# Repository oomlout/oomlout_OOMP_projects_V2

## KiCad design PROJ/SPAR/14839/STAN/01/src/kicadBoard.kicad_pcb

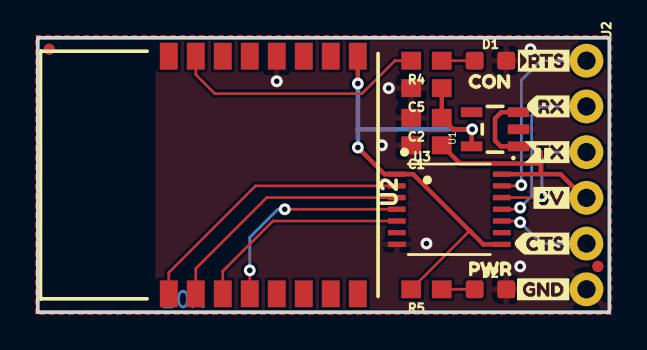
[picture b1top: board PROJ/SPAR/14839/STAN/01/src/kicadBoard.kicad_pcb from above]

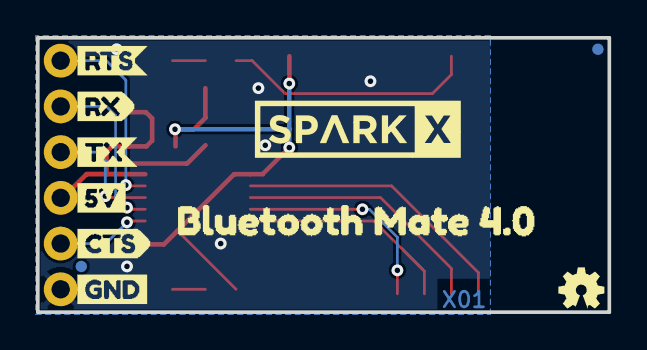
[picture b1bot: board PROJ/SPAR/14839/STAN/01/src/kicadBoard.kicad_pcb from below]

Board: 2 copper layers, 31.8 x 15.2 mm, 33 parts (11 on the bottom side), 14 nets.

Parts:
C1, C5: 1.0uF; 0603
C2: 0.1uF; 0603
D1: GREEN; LED-0603
D2: RED; LED-0603
FD1, FD2, FD3, FD4: FIDUCIALUFIDUCIAL; FIDUCIAL-MICRO
FRAME1: FRAME-LETTER; CREATIVE_COMMONS
J2: 1X06_NO_SILK
LOGO1: OSHW-LOGOMINI; OSHW-LOGO-MINI
LOGO3: SPARKX-LOGO5; SPARKX-LARGE
R4: 330; 0603
R5: 1k; 0603
U1: 3.3V; SOT23-5
U2: HM-17; HM-11
U3: TXB0104; TSSOP14
U$1: CTS13
U$2: 5V9
U$3: GND8
U$4: RX10
U$5: TX9
U$6: RTS12
U$7: RTS13
U$8: TX11
U$9: RX9
U$10: 5V6
U$11: CTS8
U$12: GND13
U$13: BLUETOOTH_MATE_4#06
U$14: PWR6
U$15: CON7

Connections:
3.3V: C2.1, C5.1, R5.2, U1.5, U2.9, U3.1, U3.8
5V: C1.1, J2.4, U1.1, U1.3, U3.14
5V_BT_CTS: J2.5, U3.10
5V_BT_RTS: J2.1, U3.13
5V_BT_RX: J2.2, U3.11
5V_BT_TX: J2.3, U3.12
BT_CTS: U2.3, U3.5
BT_RTS: U2.1, U3.2
BT_RX: U2.4, U3.4
BT_TX: U2.2, U3.3
GND: C1.2, C2.2, C5.2, D1.C, D2.C, J2.6, U1.2, U2.12, U3.7
unnamed: D1.A, R4.1
unnamed: D2.A, R5.1
PIO1/LED: R4.2, U2.15

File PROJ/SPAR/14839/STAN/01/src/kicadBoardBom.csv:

"Id";"Designator";"Package";"Quantity";"Designation";"Supplier and ref";
1;"U$15";"CON7";1;"";;;
2;"U$6";"RTS12";1;"";;;
3;"U2";"HM-11";1;"HM-17";;;
4;"FRAME1";"CREATIVE_COMMONS";1;"FRAME-LETTER";;;
5;"U$14";"PWR6";1;"";;;
6;"U$3";"GND8";1;"";;;
7;"U$1";"CTS13";1;"";;;
8;"R4";"0603";1;"330";;;
9;"D1";"LED-0603";1;"GREEN";;;
10;"U1";"SOT23-5";1;"3.3V";;;
11;"R5";"0603";1;"1k";;;
12;"C2";"0603";1;"0.1uF";;;
13;"J2";"1X06_NO_SILK";1;"";;;
14;"C1,C5";"0603";2;"1.0uF";;;
15;"U3";"TSSOP14";1;"TXB0104";;;
16;"FD1,FD2,FD4,FD3";"FIDUCIAL-MICRO";4;"FIDUCIALUFIDUCIAL";;;
17;"U$2";"5V9";1;"";;;
18;"U$4";"RX10";1;"";;;
19;"U$5";"TX9";1;"";;;
20;"D2";"LED-0603";1;"RED";;;
21;"U$12";"GND13";1;"";;;
22;"U$9";"RX9";1;"";;;
23;"U$7";"RTS13";1;"";;;
24;"LOGO1";"OSHW-LOGO-MINI";1;"OSHW-LOGOMINI";;;
25;"U$10";"5V6";1;"";;;
26;"LOGO3";"SPARKX-LARGE";1;"SPARKX-LOGO5";;;
27;"U$8";"TX11";1;"";;;
28;"U$13";"BLUETOOTH_MATE_4#06";1;"";;;
29;"U$11";"CTS8";1;"";;;

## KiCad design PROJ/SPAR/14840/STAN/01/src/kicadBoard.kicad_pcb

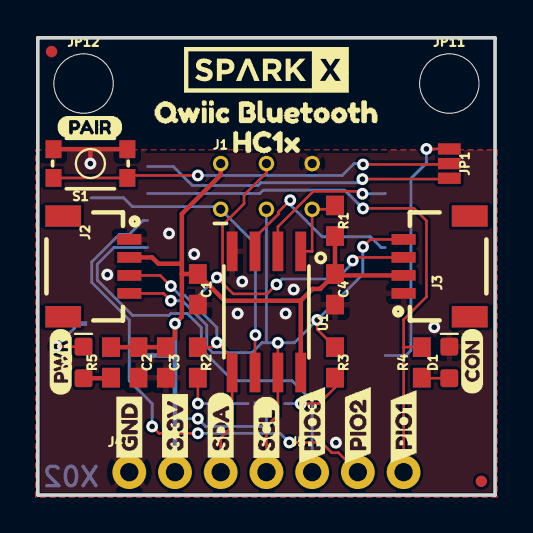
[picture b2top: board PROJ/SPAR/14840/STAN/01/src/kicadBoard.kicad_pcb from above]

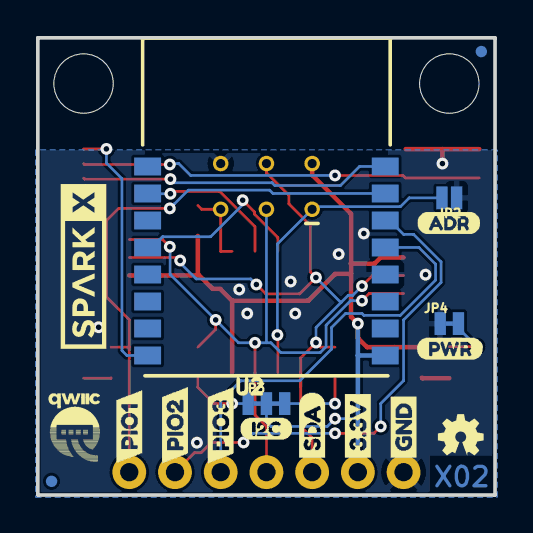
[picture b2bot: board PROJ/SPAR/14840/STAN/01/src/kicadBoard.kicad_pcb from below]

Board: 2 copper layers, 25.4 x 25.4 mm, 55 parts (18 on the bottom side), 19 nets.

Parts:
C1, C2: 0.1uF; 0603
C3: 4.7uF; 0603
C4: 10uF; 0603
D1: GREEN; LED-0603
D2: RED; LED-0603
FRAME1: FRAME-LETTER; CREATIVE_COMMONS
J1: ISP; 2X3_TEST_POINTS
J2: Qwiic-L; 1X04_1MM_RA
J3: Qwiic-R; 1X04_1MM_RA
J4: I2C; 1X04_NO_SILK
J5: PIO; 1X03_NO_SILK
JP1: Key-Select; SMT-JUMPER_3_1-NC_PASTE_NO-SILK
JP2: ADR; SMT-JUMPER_2_NO_NO-SILK
JP3: I2C; SMT-JUMPER_3_2-NC_TRACE_NO-SILK
JP4: PWR-LED; SMT-JUMPER_2_NC_TRACE_NO-SILK
JP5, JP6, JP7, JP8: FIDUCIALUFIDUCIAL; FIDUCIAL-MICRO
JP11, JP12: STAND-OFF
LOGO1: OSHW-LOGOMINI; OSHW-LOGO-MINI
LOGO2, LOGO3: SPARKX-LOGO4; SPARKX-MEDIUM
R1: 4.7k; 0603
R2, R3: 2.2k; 0603
R4: 330; 0603
R5: 1k; 0603
S1: KEY; TACTILE_SWITCH_SMD_4.6X2.8MM
U1: ATTiny85-Arduino; SO08-EIAJ_MCU
U2: HM-17; HM-11
U$1, U$6: SDA4
U$2: HC1X12
U$3, U$22: PIO110
U$4, U$10: GND0
U$5, U$11: 3#3V1
U$7: SCL2
U$8, U$14: PIO33
U$9, U$15: PIO29
U$13, U$16: PWR5
U$17: CON13
U$18: QWIIC_BLUETOOTH11
U$19: ADR8
U$20: I2C7
U$21: QWIIC-LOGO-SMALL
U$23: PAIR15

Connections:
3.3V: C1.1, C2.1, C3.1, C4.1, J1.2, J2.2, J3.2, J4.2, JP3.2, R1.2, R5.2, U1.8, U2.9
ADR: J1.1, JP2.2, U1.6
BT-RXI: U1.3, U2.4
BT-TXO: U1.2, U2.2
GND: C1.2, C2.2, C3.2, C4.2, D1.C, J1.6, J2.1, J3.1, J4.1, JP2.1, JP4.1, S1.1, S1.2, U1.4, U2.12
KEY-HM17: JP1.1, U2.8
unnamed: D2.C, JP4.2
unnamed: D1.A, R4.1
unnamed: D2.A, R5.1
unnamed: JP1.2, S1.3, S1.4
PIO0/KEY-HM11: JP1.3, U2.16
PIO1/LED: J5.3, R4.2, U2.15
PIO2: J5.2, U2.14
PIO3: J5.1, U2.13
SCL: J1.3, J2.4, J3.4, J4.4, R3.1, U1.7
SCL_PU1: JP3.1, R3.2
SDA: J1.4, J2.3, J3.3, J4.3, R2.1, U1.5
SDA_PU1: JP3.3, R2.2
~RST: J1.5, R1.1, U1.1

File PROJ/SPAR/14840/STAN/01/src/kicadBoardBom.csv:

"Id";"Designator";"Package";"Quantity";"Designation";"Supplier and ref";
1;"C4";"0603";1;"10uF";;;
2;"R4";"0603";1;"330";;;
3;"C2,C1";"0603";2;"0.1uF";;;
4;"R3,R2";"0603";2;"2.2k";;;
5;"U$17";"CON13";1;"";;;
6;"J3";"1X04_1MM_RA";1;"Qwiic-R";;;
7;"JP11,JP12";"STAND-OFF";2;"STAND-OFF";;;
8;"C3";"0603";1;"4.7uF";;;
9;"FRAME1";"CREATIVE_COMMONS";1;"FRAME-LETTER";;;
10;"U$16,U$13";"PWR5";2;"";;;
11;"JP1";"SMT-JUMPER_3_1-NC_PASTE_NO-SILK";1;"Key-Select";;;
12;"U$2";"HC1X12";1;"";;;
13;"U$5,U$11";"3#3V1";2;"";;;
14;"U$18";"QWIIC_BLUETOOTH11";1;"";;;
15;"LOGO3,LOGO2";"SPARKX-MEDIUM";2;"SPARKX-LOGO4";;;
16;"J4";"1X04_NO_SILK";1;"I2C";;;
17;"D1";"LED-0603";1;"GREEN";;;
18;"JP6,JP7,JP8,JP5";"FIDUCIAL-MICRO";4;"FIDUCIALUFIDUCIAL";;;
19;"U1";"SO08-EIAJ_MCU";1;"ATTiny85-Arduino";;;
20;"U$8,U$14";"PIO33";2;"";;;
21;"R1";"0603";1;"4.7k";;;
22;"J1";"2X3_TEST_POINTS";1;"ISP";;;
23;"U$3,U$22";"PIO110";2;"";;;
24;"R5";"0603";1;"1k";;;
25;"J2";"1X04_1MM_RA";1;"Qwiic-L";;;
26;"U$23";"PAIR15";1;"";;;
27;"U$6,U$1";"SDA4";2;"";;;
28;"S1";"TACTILE_SWITCH_SMD_4.6X2.8MM";1;"KEY";;;
29;"D2";"LED-0603";1;"RED";;;
30;"U$9,U$15";"PIO29";2;"";;;
31;"U$4,U$10";"GND0";2;"";;;
32;"J5";"1X03_NO_SILK";1;"PIO";;;
33;"U$7";"SCL2";1;"";;;
34;"U$21";"QWIIC-LOGO-SMALL";1;"";;;
35;"U2";"HM-11";1;"HM-17";;;
36;"JP4";"SMT-JUMPER_2_NC_TRACE_NO-SILK";1;"PWR-LED";;;
37;"JP2";"SMT-JUMPER_2_NO_NO-SILK";1;"ADR";;;
38;"U$20";"I2C7";1;"";;;
39;"JP3";"SMT-JUMPER_3_2-NC_TRACE_NO-SILK";1;"I2C";;;
40;"LOGO1";"OSHW-LOGO-MINI";1;"OSHW-LOGOMINI";;;
41;"U$19";"ADR8";1;"";;;

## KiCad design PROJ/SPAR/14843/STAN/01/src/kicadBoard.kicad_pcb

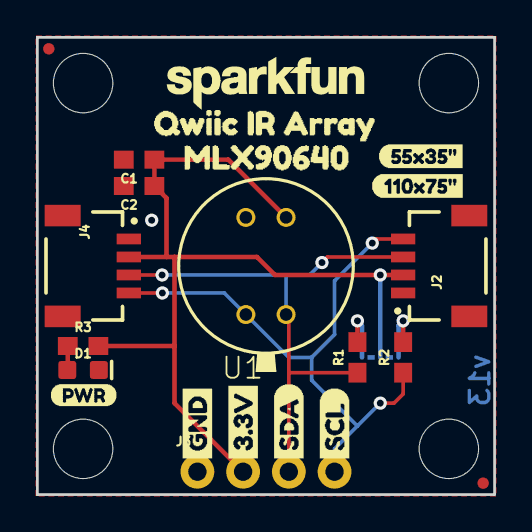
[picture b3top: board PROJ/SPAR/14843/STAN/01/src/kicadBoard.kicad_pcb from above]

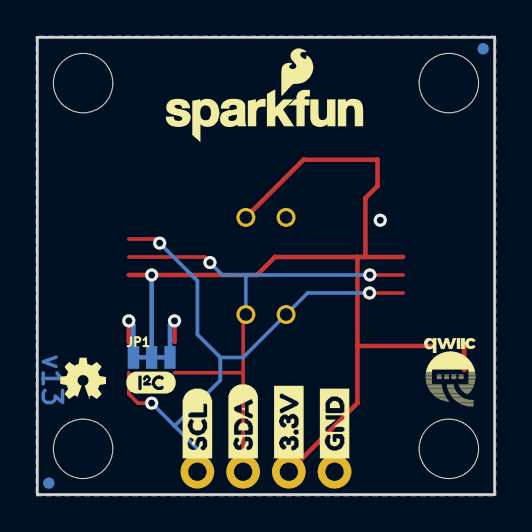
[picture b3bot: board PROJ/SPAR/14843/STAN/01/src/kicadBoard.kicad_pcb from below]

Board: 2 copper layers, 25.4 x 25.4 mm, 39 parts (11 on the bottom side), 7 nets.

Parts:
C1: 0.1uF; 0603
C2: 1.0uF; 0603
D1: RED; LED-0603
FRAME1: FRAME-LETTER; CREATIVE_COMMONS
J2, J4: JST04_1MM_RA
J3: PTH; 1X04_NO_SILK
JP1: I2C; SMT-JUMPER_3_2-NC_TRACE_NO-SILK
JP2, JP5, JP6, JP7: FIDUCIALUFIDUCIAL; MICRO-FIDUCIAL
JP3, JP4, JP8, JP9: STAND-OFF
LOGO1: OSHW-LOGOMINI; OSHW-LOGO-MINI
LOGO2: SFE_LOGO_NAME_FLAME.1_INCH; SFE_LOGO_NAME_FLAME_.1
LOGO3: SFE_LOGO_NAME.1_INCH; SFE_LOGO_NAME_.1
LOGO4: REVISION
R1, R2: 2.2k; 0603
R3: 1k; 0603
U1: 110DEG; MLX90540_MLX90640
U$1, U$7: SDA-[)
U$3: 55X35#1
U$4, U$8: SCL-[)
U$5, U$9: 3.3V
U$6, U$10: GND-04
U$11: QWIIC-LOGO-SMALL
U$12: PWR-()-03
U$13: MLX906401
U$14: QWIIC_IR_ARRAY0
U$15: 110X75#0
U$16: I_SUPER2_C-()-03

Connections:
3.3V: C1.1, C2.1, J2.2, J3.2, J4.2, JP1.2, R3.2, U1.VDD
GND: C1.2, C2.2, D1.C, J2.1, J3.1, J4.1, U1.GND
unnamed: JP1.3, R1.2
unnamed: JP1.1, R2.2
unnamed: D1.A, R3.1
SCL: J2.4, J3.4, J4.4, R2.1, U1.SCL
SDA: J2.3, J3.3, J4.3, R1.1, U1.SDA

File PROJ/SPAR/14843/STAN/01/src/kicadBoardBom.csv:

"Id";"Designator";"Package";"Quantity";"Designation";"Supplier and ref";
1;"J2,J4";"JST04_1MM_RA";2;"";;;
2;"R3";"0603";1;"1k";;;
3;"C2";"0603";1;"1.0uF";;;
4;"U$4,U$8";"SCL-[)";2;"";;;
5;"U$13";"MLX906401";1;"";;;
6;"U$15";"110X75#0";1;"";;;
7;"U$14";"QWIIC_IR_ARRAY0";1;"";;;
8;"U$6,U$10";"GND-04";2;"";;;
9;"JP9,JP8,JP3,JP4";"STAND-OFF";4;"STAND-OFF";;;
10;"U$3";"55X35#1";1;"";;;
11;"U1";"MLX90540_MLX90640";1;"110DEG";;;
12;"U$12";"PWR-()-03";1;"";;;
13;"U$5,U$9";"3.3V";2;"";;;
14;"C1";"0603";1;"0.1uF";;;
15;"J3";"1X04_NO_SILK";1;"PTH";;;
16;"JP2,JP5,JP6,JP7";"MICRO-FIDUCIAL";4;"FIDUCIALUFIDUCIAL";;;
17;"D1";"LED-0603";1;"RED";;;
18;"R2,R1";"0603";2;"2.2k";;;
19;"LOGO4";"REVISION";1;"REVISION";;;
20;"LOGO3";"SFE_LOGO_NAME_.1";1;"SFE_LOGO_NAME.1_INCH";;;
21;"FRAME1";"CREATIVE_COMMONS";1;"FRAME-LETTER";;;
22;"U$1,U$7";"SDA-[)";2;"";;;
23;"U$11";"QWIIC-LOGO-SMALL";1;"";;;
24;"LOGO1";"OSHW-LOGO-MINI";1;"OSHW-LOGOMINI";;;
25;"JP1";"SMT-JUMPER_3_2-NC_TRACE_NO-SILK";1;"I2C";;;
26;"LOGO2";"SFE_LOGO_NAME_FLAME_.1";1;"SFE_LOGO_NAME_FLAME.1_INCH";;;
27;"U$16";"I_SUPER2_C-()-03";1;"";;;

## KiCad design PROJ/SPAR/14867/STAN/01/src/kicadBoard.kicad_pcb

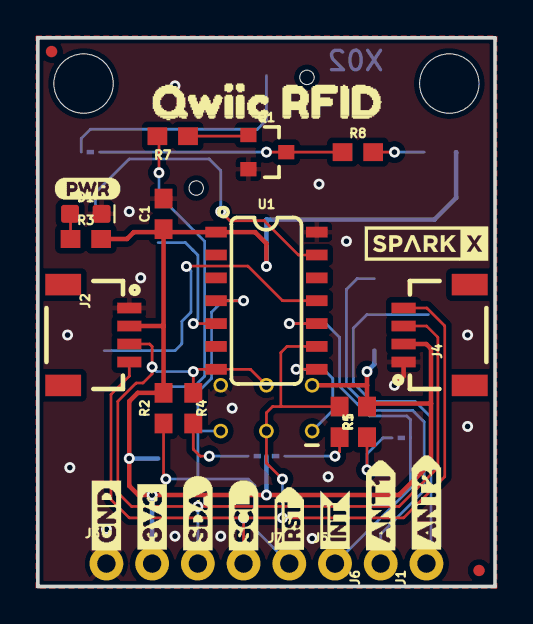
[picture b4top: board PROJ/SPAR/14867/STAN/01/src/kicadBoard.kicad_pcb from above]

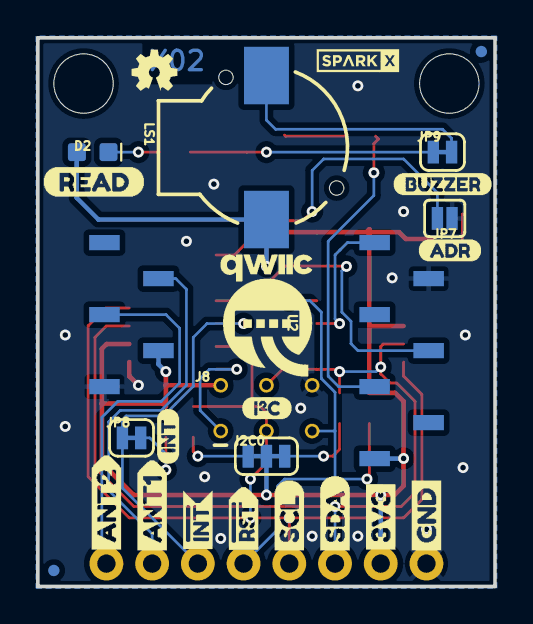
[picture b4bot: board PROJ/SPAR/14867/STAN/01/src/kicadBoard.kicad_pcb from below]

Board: 2 copper layers, 25.4 x 30.5 mm, 60 parts (26 on the bottom side), 21 nets.

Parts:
C1: 0.1uF; 0603
D1: RED; LED-0603
D2: BLUE; LED-0603
FRAME1: FRAME-LETTER; CREATIVE_COMMONS
I2C0: SMT-JUMPER_3_2-NC_TRACE_SILK
J1, J5, J6, J7: 1X01_NO_SILK
J2, J4: 1X04_1MM_RA
J3: PTH; 1X04_NO_SILK
J8: AVR_SPI_PROG_3X2TESTPOINTS; 2X3_TEST_POINTS
JP1, JP2, JP5, JP6: FIDUCIALUFIDUCIAL; MICRO-FIDUCIAL
JP3, JP4: STAND-OFF
JP7: ADR; SMT-JUMPER_2_NO_SILK
JP8: INT; SMT-JUMPER_2_NC_TRACE_SILK
JP9: BUZZ; SMT-JUMPER_2_NC_TRACE_SILK
LOGO1: OSHW-LOGOMINI; OSHW-LOGO-MINI
LS1: BUZZER-SMD; BUZZER-CCV
Q1: 600mA/40V; SOT23-3
R1, R2: 10k; 0603
R3, R7, R8: 1k; 0603
R4, R5: 2.2k; 0603
U1: ATTINY84-ARDUINO; SO14
U2: ID-12/20SMD; ID-12_SMD
U$1: SPARKX-TINY
U$2: I_SUPER2_C-()-03
U$3, U$17: ANT20
U$4: SPARKX-LOGO3; SPARKX-SMALL
U$5, U$26: RST#-[_
U$6, U$23: SDA-[)
U$7, U$22: SCL-[)
U$8: QWIIC-LOGO-MEDIUM
U$9, U$25: GND-04
U$10, U$24: 3V3-04
U$11, U$21: INT#-[_
U$12: ADR0
U$13: INT0
U$14: PWR-()-03
U$15: BUZZER0
U$16, U$20: ANT10
U$18: READ0
U$19: QWIIC_RFID0

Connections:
3.3V: C1.1, D2.A, I2C0.2, J2.2, J3.2, J4.2, J8.2, LS1.+, R1.2, R2.2, R3.2, U1.1, U2.2, U2.11
ANT1: J1.1, U2.3
ANT2: J6.1, U2.4
DATA_UART: U1.11, U2.9
GND: C1.2, D1.C, J2.1, J3.1, J4.1, J8.6, JP7.1, Q1.2, U1.14, U2.1, U2.7
LED_BUZZ: R7.2, U2.10
MISO: J8.1, U1.8
unnamed: I2C0.1, R5.2
unnamed: I2C0.3, R4.2
unnamed: D1.A, R3.1
unnamed: JP8.2, R1.1
unnamed: D2.C, R8.2
unnamed: JP7.2, U1.13
unnamed: Q1.1, R7.1
unnamed: JP9.1, Q1.3, R8.1
unnamed: JP9.2, LS1.-
SCL/SCK: J2.4, J3.4, J4.4, J8.3, R5.1, U1.9
SDA/MOSI: J2.3, J3.3, J4.3, J8.4, R4.1, U1.7
TAG_IN_RANGE: U1.5, U2.6
~INT: J5.1, JP8.1, U1.10
~RST: J7.1, J8.5, R2.1, U1.4

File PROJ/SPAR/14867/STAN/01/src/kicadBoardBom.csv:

"Id";"Designator";"Package";"Quantity";"Designation";"Supplier and ref";
1;"FRAME1";"CREATIVE_COMMONS";1;"FRAME-LETTER";;;
2;"J2,J4";"1X04_1MM_RA";2;"";;;
3;"U1";"SO14";1;"ATTINY84-ARDUINO";;;
4;"U$9,U$25";"GND-04";2;"";;;
5;"R8,R3,R7";"0603";3;"1k";;;
6;"JP6,JP2,JP5,JP1";"MICRO-FIDUCIAL";4;"FIDUCIALUFIDUCIAL";;;
7;"JP3,JP4";"STAND-OFF";2;"STAND-OFF";;;
8;"J7,J1,J6,J5";"1X01_NO_SILK";4;"";;;
9;"Q1";"SOT23-3";1;"600mA/40V";;;
10;"R4,R5";"0603";2;"2.2k";;;
11;"R1,R2";"0603";2;"10k";;;
12;"U$17,U$3";"ANT20";2;"";;;
13;"D1";"LED-0603";1;"RED";;;
14;"U$6,U$23";"SDA-[)";2;"";;;
15;"U$19";"QWIIC_RFID0";1;"";;;
16;"U$4";"SPARKX-SMALL";1;"SPARKX-LOGO3";;;
17;"J3";"1X04_NO_SILK";1;"PTH";;;
18;"C1";"0603";1;"0.1uF";;;
19;"U$7,U$22";"SCL-[)";2;"";;;
20;"U$14";"PWR-()-03";1;"";;;
21;"U$11,U$21";"INT#-[_";2;"";;;
22;"U$16,U$20";"ANT10";2;"";;;
23;"U$5,U$26";"RST#-[_";2;"";;;
24;"U$10,U$24";"3V3-04";2;"";;;
25;"U2";"ID-12_SMD";1;"ID-12/20SMD";;;
26;"D2";"LED-0603";1;"BLUE";;;
27;"JP9";"SMT-JUMPER_2_NC_TRACE_SILK";1;"BUZZ";;;
28;"I2C0";"SMT-JUMPER_3_2-NC_TRACE_SILK";1;"";;;
29;"LOGO1";"OSHW-LOGO-MINI";1;"OSHW-LOGOMINI";;;
30;"JP8";"SMT-JUMPER_2_NC_TRACE_SILK";1;"INT";;;
31;"JP7";"SMT-JUMPER_2_NO_SILK";1;"ADR";;;
32;"J8";"2X3_TEST_POINTS";1;"AVR_SPI_PROG_3X2TESTPOINTS";;;
33;"U$1";"SPARKX-TINY";1;"";;;
34;"LS1";"BUZZER-CCV";1;"BUZZER-SMD";;;
35;"U$8";"QWIIC-LOGO-MEDIUM";1;"";;;
36;"U$2";"I_SUPER2_C-()-03";1;"";;;
37;"U$13";"INT0";1;"";;;
38;"U$12";"ADR0";1;"";;;
39;"U$18";"READ0";1;"";;;
40;"U$15";"BUZZER0";1;"";;;

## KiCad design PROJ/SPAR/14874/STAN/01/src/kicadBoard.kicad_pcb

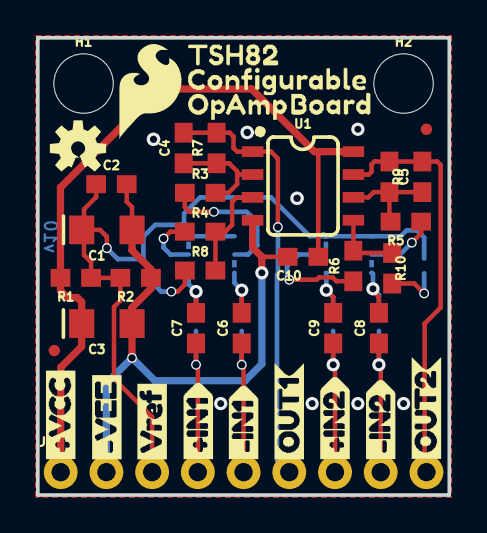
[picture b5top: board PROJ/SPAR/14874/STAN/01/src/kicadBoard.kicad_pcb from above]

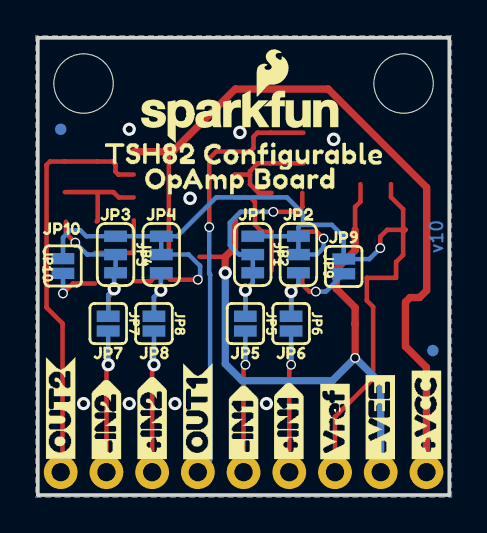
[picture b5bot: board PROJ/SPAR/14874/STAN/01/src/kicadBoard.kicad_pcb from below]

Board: 2 copper layers, 22.9 x 25.4 mm, 78 parts (36 on the bottom side), 23 nets.

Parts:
C1, C3: 10uF; EIA3216
C2, C10: 0.1uF; 0603
C4, C5: DNP; 0603
C6, C7, C8, C9: 1.0uF; 0603
FD1, FD2, FD3, FD4: FIDUCIALUFIDUCIAL; FIDUCIAL-MICRO
FRAME1: FRAME-LETTER; CREATIVE_COMMONS
H1, H2: STAND-OFF
J1: 1X09_NO_SILK
JP1, JP2, JP3, JP4: JUMPER-SMT_3_1-NC_TRACE_SILK; SMT-JUMPER_3_1-NC_TRACE_SILK
JP5, JP6, JP7, JP8, JP9, JP10: JUMPER-SMT_2_NO_SILK; SMT-JUMPER_2_NO_SILK
LOGO1: SFE_LOGO_FLAME.2_INCH; SFE_LOGO_FLAME_.2
LOGO2: SFE_LOGO_NAME_FLAME.1_INCH; SFE_LOGO_NAME_FLAME_.1
LOGO3: OSHW-LOGOS; OSHW-LOGO-S
R1, R2: 2.2k; 0603
R3, R4, R5, R6: 10k; 0603
R7, R8, R9, R10: 47k; 0603
U1: TSH82; SO08
U$1, U$2: #VEE1
U$3, U$30: #VCC0
U$4, U$5: VREF6
U$6, U$7: #IN12
U$8, U$9: #IN13
U$10, U$11: OUT17
U$12, U$13: #IN24
U$14, U$16: #IN25
U$15, U$17: OUT28
U$18: JP10
U$19: JP21
U$20: JP32
U$21: JP43
U$22, U$26: TSH820
U$23, U$27: CONFIGURABLE1
U$24, U$28: OPAMP2
U$25, U$29: BOARD3
U$31: JP54
U$32: JP65
U$33: JP76
U$34: JP87
U$35: JP98
U$36: JP109

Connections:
+IN1: C7.1, J1.4, JP6.2
+IN2: C9.1, J1.7, JP8.2
-IN1: C6.1, J1.5, JP5.2
-IN2: C8.1, J1.8, JP7.2
unnamed: C4.1, R3.2, R7.1, U1.2
unnamed: R4.2, R8.2, U1.3
unnamed: JP9.1, R8.1
unnamed: JP1.2, R3.1
unnamed: JP2.2, R4.1
unnamed: C6.2, JP1.3, JP5.1
unnamed: C7.2, JP2.1, JP6.1
unnamed: C8.2, JP3.3, JP7.1
unnamed: JP3.2, R5.1
unnamed: C5.1, R5.2, R9.2, U1.6
unnamed: JP4.2, R6.1
unnamed: C9.2, JP4.1, JP8.1
unnamed: R6.2, R10.1, U1.5
unnamed: JP10.1, R10.2
OUT1: C4.2, J1.6, R7.2, U1.1
OUT2: C5.2, J1.9, R9.1, U1.7
VCC: C3.+, C10.1, J1.1, R1.2, U1.8
VNEG: C1.-, C2.2, C3.-, C10.2, J1.2, R2.1, U1.4
VREF: C1.+, C2.1, J1.3, JP1.1, JP2.3, JP3.1, JP4.3, JP9.2, JP10.2, R1.1, R2.2

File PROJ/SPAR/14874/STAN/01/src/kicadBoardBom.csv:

"Id";"Designator";"Package";"Quantity";"Designation";"Supplier and ref";
1;"FRAME1";"CREATIVE_COMMONS";1;"FRAME-LETTER";;;
2;"R3,R6,R4,R5";"0603";4;"10k";;;
3;"R9,R8,R10,R7";"0603";4;"47k";;;
4;"LOGO1";"SFE_LOGO_FLAME_.2";1;"SFE_LOGO_FLAME.2_INCH";;;
5;"C10,C2";"0603";2;"0.1uF";;;
6;"U$10,U$11";"OUT17";2;"";;;
7;"U$1,U$2";"#VEE1";2;"";;;
8;"U1";"SO08";1;"TSH82";;;
9;"C7,C8,C9,C6";"0603";4;"1.0uF";;;
10;"H2,H1";"STAND-OFF";2;"STAND-OFF";;;
11;"U$4,U$5";"VREF6";2;"";;;
12;"U$24,U$28";"OPAMP2";2;"";;;
13;"U$8,U$9";"#IN13";2;"";;;
14;"U$23,U$27";"CONFIGURABLE1";2;"";;;
15;"C1,C3";"EIA3216";2;"10uF";;;
16;"C5,C4";"0603";2;"DNP";;;
17;"R2,R1";"0603";2;"2.2k";;;
18;"U$7,U$6";"#IN12";2;"";;;
19;"FD1,FD2,FD4,FD3";"FIDUCIAL-MICRO";4;"FIDUCIALUFIDUCIAL";;;
20;"U$25,U$29";"BOARD3";2;"";;;
21;"LOGO3";"OSHW-LOGO-S";1;"OSHW-LOGOS";;;
22;"J1";"1X09_NO_SILK";1;"";;;
23;"U$3,U$30";"#VCC0";2;"";;;
24;"U$22,U$26";"TSH820";2;"";;;
25;"U$14,U$16";"#IN25";2;"";;;
26;"U$12,U$13";"#IN24";2;"";;;
27;"U$15,U$17";"OUT28";2;"";;;
28;"U$34";"JP87";1;"";;;
29;"JP8,JP9,JP10,JP6,JP5,JP7";"SMT-JUMPER_2_NO_SILK";6;"JUMPER-SMT_2_NO_SILK";;;
30;"U$36";"JP109";1;"";;;
31;"U$19";"JP21";1;"";;;
32;"U$20";"JP32";1;"";;;
33;"LOGO2";"SFE_LOGO_NAME_FLAME_.1";1;"SFE_LOGO_NAME_FLAME.1_INCH";;;
34;"U$21";"JP43";1;"";;;
35;"JP3,JP2,JP1,JP4";"SMT-JUMPER_3_1-NC_TRACE_SILK";4;"JUMPER-SMT_3_1-NC_TRACE_SILK";;;
36;"U$35";"JP98";1;"";;;
37;"U$32";"JP65";1;"";;;
38;"U$18";"JP10";1;"";;;
39;"U$33";"JP76";1;"";;;
40;"U$31";"JP54";1;"";;;

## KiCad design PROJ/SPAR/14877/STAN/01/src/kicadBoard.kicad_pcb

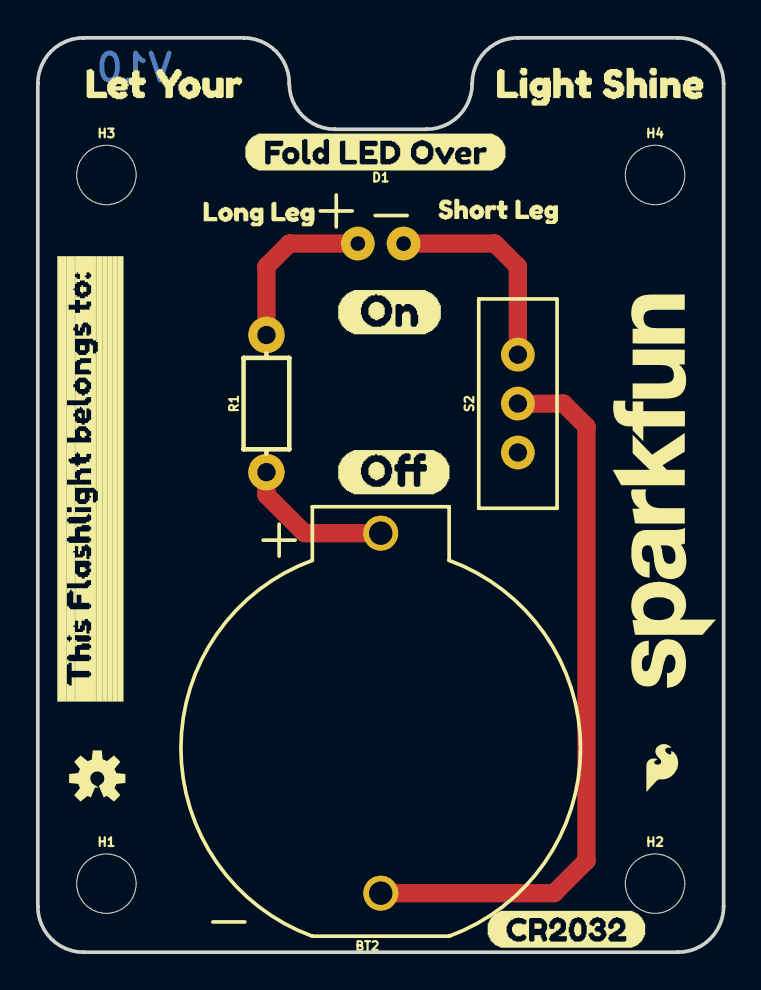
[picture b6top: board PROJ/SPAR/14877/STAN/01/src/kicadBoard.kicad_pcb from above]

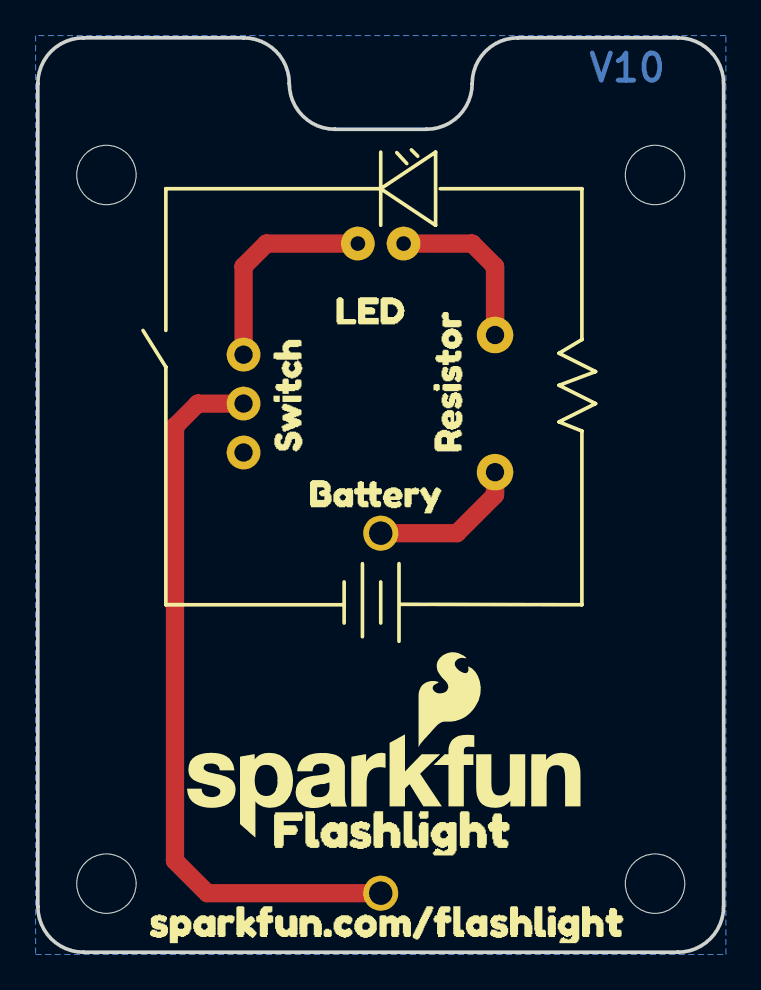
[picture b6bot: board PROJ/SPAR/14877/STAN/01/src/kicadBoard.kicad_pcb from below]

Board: 2 copper layers, 38.1 x 50.8 mm, 28 parts (7 on the bottom side), 4 nets.

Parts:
BT2: BATTCOM_20MM_PTH_KIT
D1: LED_5MM-KIT-NO-SILK
FRAME1: FRAME-LETTER; CREATIVE_COMMONS
H1, H2, H3, H4: STAND-OFF
LOGO1: OSHW-LOGOS; OSHW-LOGO-S
LOGO2: SFE_LOGO_FLAME.1_INCH; SFE_LOGO_FLAME_.1
LOGO3: SFE_LOGO_NAME_FLAME.2_INCH; SFE_LOGO_NAME_FLAME_.2
LOGO4: SFE_LOGO_NAME.2_INCH; SFE_LOGO_NAME_.2
R1: 10; AXIAL-0.3-KIT
S2: SWITCH_SPDT_PTH_11.6X4.0MM_KIT
U$1: CR20325
U$2: FLASHLIGHT6
U$3: FOLD_LED_OVER0
U$4: BATTERY11
U$5: LET_YOUR11
U$6: LIGHT_SHINE12
U$7: LONG_LEG2
U$8: OFF4
U$9: ON3
U$10: SHORT_LEG1
U$11: SPARKFUN#COM#FLASHLIGHT13
U$12: LED12
U$13: THIS_FLASHLIGHT_BELONGS_TO#10
U$14: RESISTOR14
U$15: SWITCH13

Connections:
ANODE: D1.K, S2.1
CATHODE: BT2.1, R1.P$1
GND: D1.A, R1.P$2
unnamed: BT2.2, S2.2

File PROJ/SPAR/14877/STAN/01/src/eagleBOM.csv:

"Part";"Value";"Device";"Package";"Description";"PROD_ID";"SF_SKU";"VALUE";
"BT2";"";"BATTERY-20MM_PTH_KIT";"BATTCOM_20MM_PTH_KIT";"Battery - Single Cell";"9031";"";"";
"D1";"";"LED-5MM-KIT-NO-SILK";"LED_5MM-KIT-NO-SILK";"LED (Generic)";"9903";"";"";
"FRAME1";"FRAME-LETTER";"FRAME-LETTER";"CREATIVE_COMMONS";"Schematic Frame - Letter";"";"";"";
"H1";"STAND-OFF";"STAND-OFF";"STAND-OFF";"Stand Off";"";"";"";
"H2";"STAND-OFF";"STAND-OFF";"STAND-OFF";"Stand Off";"";"";"";
"H3";"STAND-OFF";"STAND-OFF";"STAND-OFF";"Stand Off";"";"";"";
"H4";"STAND-OFF";"STAND-OFF";"STAND-OFF";"Stand Off";"";"";"";
"LOGO1";"OSHW-LOGOS";"OSHW-LOGOS";"OSHW-LOGO-S";"Open-Source Hardware (OSHW) Logo";"";"";"";
"LOGO2";"SFE_LOGO_FLAME.1_INCH";"SFE_LOGO_FLAME.1_INCH";"SFE_LOGO_FLAME_.1";"SparkFun Flame Logo";"";"";"";
"LOGO3";"SFE_LOGO_NAME_FLAME.2_INCH";"SFE_LOGO_NAME_FLAME.2_INCH";"SFE_LOGO_NAME_FLAME_.2";"SparkFun Font Logo w/ Flame";"";"";"";
"LOGO4";"SFE_LOGO_NAME.2_INCH";"SFE_LOGO_NAME.2_INCH";"SFE_LOGO_NAME_.2";"SparkFun Font Logo";"";"";"";
"R1";"10";"RESISTORAXIAL-0.3-KIT";"AXIAL-0.3-KIT";"Generic Resistor Package";"8371";"";" ";
"S2";"";"SWITCH-SPDT-PTH-11.6X4.0MM-KIT";"SWITCH_SPDT_PTH_11.6X4.0MM_KIT";"Single Pole, Double Throw (SPDT) Switch";"SWCH-08261";"COM-00102";"";

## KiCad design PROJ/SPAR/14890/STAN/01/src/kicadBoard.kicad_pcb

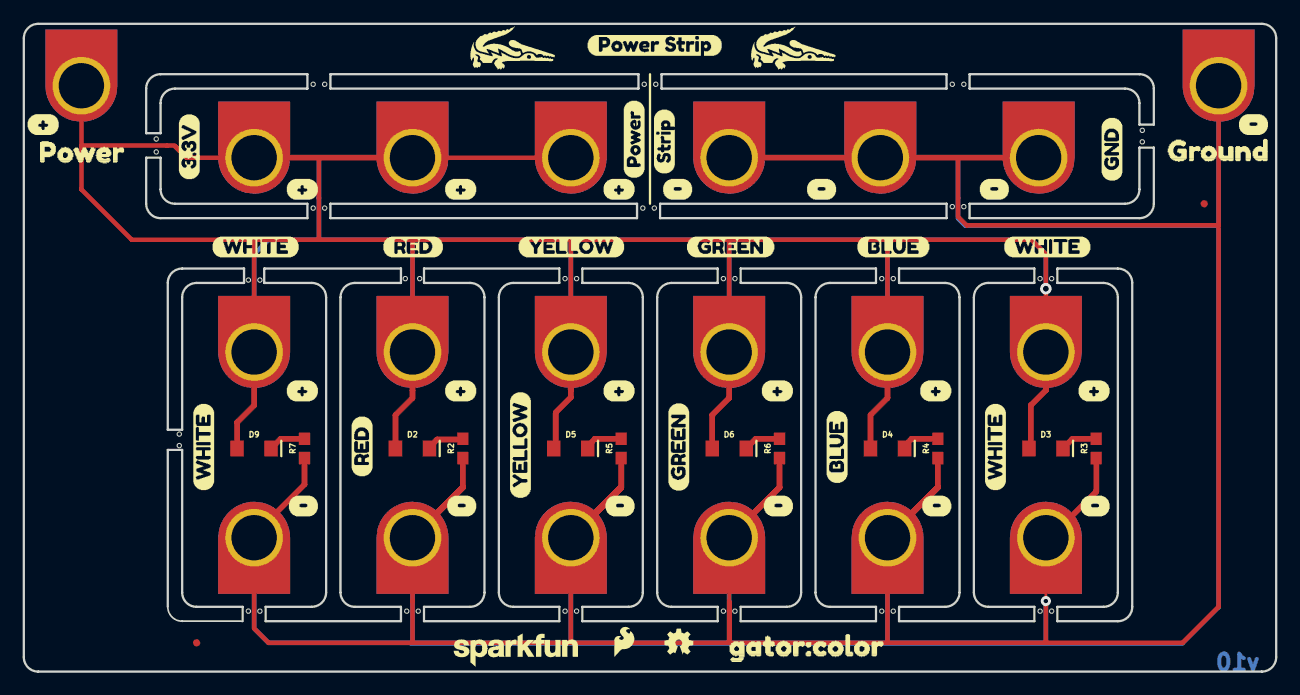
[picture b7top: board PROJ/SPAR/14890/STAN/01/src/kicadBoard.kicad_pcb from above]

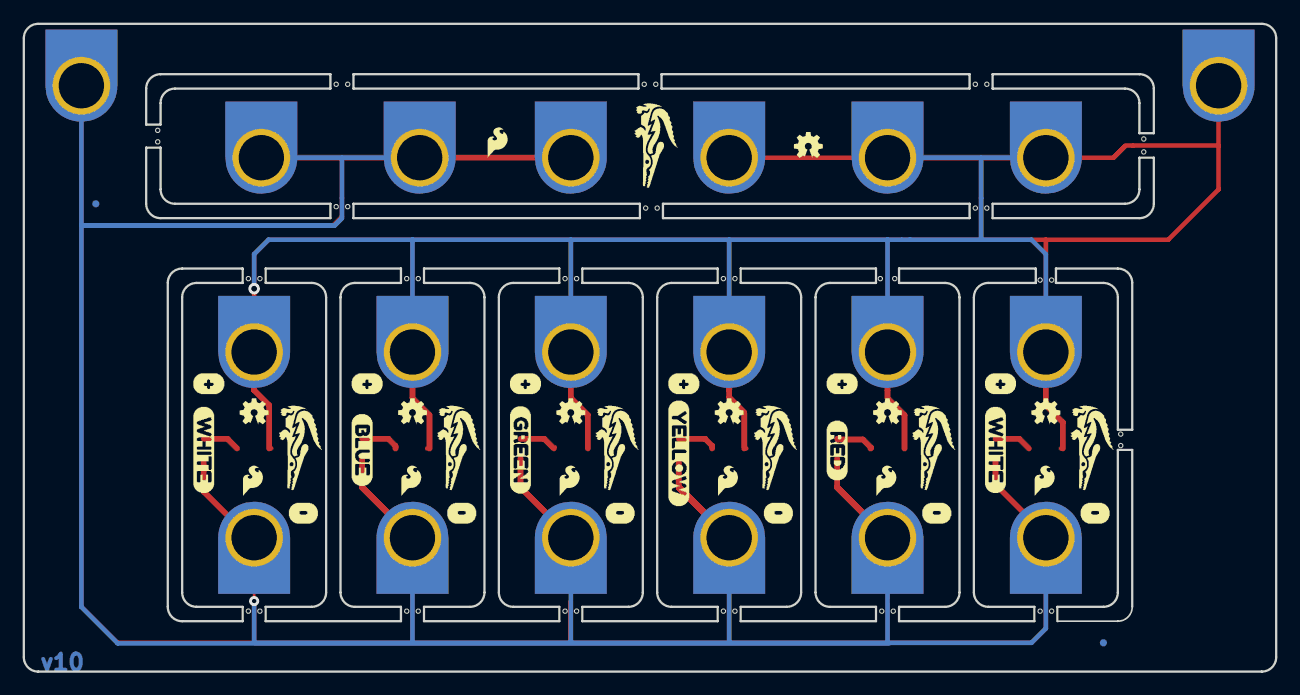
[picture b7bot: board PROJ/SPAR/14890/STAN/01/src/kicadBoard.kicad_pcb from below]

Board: 2 copper layers, 110.5 x 57.1 mm, 165 parts (41 on the bottom side), 8 nets.

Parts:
@HOLE0, @HOLE1, @HOLE2, @HOLE3, @HOLE4, @HOLE5, @HOLE6, @HOLE7, @HOLE8, @HOLE9, @HOLE10, @HOLE11, @HOLE12, @HOLE13, @HOLE14, @HOLE15, @HOLE16, @HOLE17, @HOLE18, @HOLE19, @HOLE20, @HOLE21, @HOLE22, @HOLE23, @HOLE24, @HOLE25, @HOLE26, @HOLE27, @HOLE28, @HOLE29, @HOLE30, @HOLE31, @HOLE32, @HOLE33, @HOLE34, @HOLE35, @HOLE36, @HOLE37, @HOLE38, @HOLE39, @HOLE40, @HOLE41: (no value)
D2: RED; LED-1206
D3, D9: WHITE; LED-1206
D4: BLUE; LED-1206
D5: Yellow; LED-1206
D6: GREEN; LED-1206
FD1, FD2, FD3, FD4: FIDUCIALUFIDUCIAL; FIDUCIAL-MICRO
FRAME1: FRAME-LETTER; CREATIVE_COMMONS
LOGO1, LOGO9, LOGO10, LOGO11, LOGO12, LOGO13, LOGO17, LOGO19: SFE_LOGO_FLAME.1_INCH; SFE_LOGO_FLAME_.1
LOGO2, LOGO3, LOGO4, LOGO5, LOGO6, LOGO7, LOGO15, LOGO18: OSHW-LOGOMINI; OSHW-LOGO-MINI
LOGO8: REVISION
LOGO16: SFE_LOGO_NAME.1_INCH; SFE_LOGO_NAME_.1
R2, R3, R5, R7: 330; 0603
R4, R6: 150; 0603
U$1, U$2, U$3, U$6, U$7, U$8, U$10, U$11, U$13, U$16, U$18, U$19, U$20, U$21, U$28, U$30, U$32, U$33, U$34, U$38: TAB_GATOR_MINI
U$4: ORDERING_INSTRUCTIONS
U$5: POWER_STRIP0
U$9: GROUND3
U$12, U$14, U$15, U$53, U$55, U$57, U$60, U$62, U$64, U$77, U$81, U$83, U$84, U$85, U$86, U$87: #8
U$17, U$41, U$42: RED2
U$22, U$23, U$24, U$54, U$56, U$58, U$61, U$63, U$65, U$82, U$89, U$90, U$91, U$92, U$93, U$95: #9
U$25: 3#3V1
U$26: GND0
U$27: POWER1
U$29, U$31, U$50, U$68, U$69, U$70, U$71, U$72, U$73: GATOR#PNG
U$35: STRIP2
U$36, U$37, U$75: BLUE4
U$39, U$40, U$67: GREEN3
U$43: POWER2
U$44, U$45, U$46, U$47, U$78, U$79: WHITE6
U$48, U$49, U$76: YELLOW5
U$51: GATOR#COLOR0

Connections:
3.3V: D2.A, D3.A, D4.A, D5.A, D6.A, D9.A, U$10.P1, U$13.P1, U$16.P1, U$18.P1, U$19.P1, U$20.P1, U$21.P1, U$32.P1, U$33.P1, U$34.P1
GND: R2.1, R3.1, R4.1, R5.1, R6.1, R7.1, U$1.P1, U$2.P1, U$3.P1, U$6.P1, U$7.P1, U$8.P1, U$11.P1, U$28.P1, U$30.P1, U$38.P1
unnamed: D2.C, R2.2
unnamed: D3.C, R3.2
unnamed: D4.C, R4.2
unnamed: D5.C, R5.2
unnamed: D6.C, R6.2
unnamed: D9.C, R7.2

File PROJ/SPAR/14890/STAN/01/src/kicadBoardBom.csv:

"Id";"Designator";"Package";"Quantity";"Designation";"Supplier and ref";
1;"U$14,U$62,U$77,U$53,U$60,U$57,U$15,U$55,U$64,U$12,U$87,U$83,U$85,U$86,U$81,U$84";"#8";16;"";;;
2;"@HOLE3,@HOLE16,@HOLE0,@HOLE15,@HOLE2,@HOLE10,@HOLE21,@HOLE25,@HOLE40,@HOLE17,@HOLE13,@HOLE26,@HOLE5,@HOLE24,@HOLE7,@HOLE36,@HOLE28,@HOLE14,@HOLE39,@HOLE31,@HOLE22,@HOLE6,@HOLE35,@HOLE32,@HOLE4,@HOLE1,@HOLE29,@HOLE19,@HOLE38,@HOLE9,@HOLE11,@HOLE23,@HOLE34,@HOLE33,@HOLE12,@HOLE8,@HOLE27,@HOLE41,@HOLE30,@HOLE37,@HOLE18,@HOLE20";"";42;"";;;
3;"U$95,U$56,U$61,U$63,U$65,U$58,U$54,U$22,U$24,U$23,U$89,U$90,U$93,U$92,U$82,U$91";"#9";16;"";;;
4;"U$49,U$48,U$76";"YELLOW5";3;"";;;
5;"U$10,U$1,U$8,U$13,U$30,U$19,U$33,U$32,U$21,U$34,U$11,U$7,U$38,U$6,U$20,U$2,U$28,U$18,U$3,U$16";"TAB_GATOR_MINI";20;"TAB_GATOR_MINI";;;
6;"U$25";"3#3V1";1;"";;;
7;"U$27";"POWER1";1;"";;;
8;"U$47,U$45,U$46,U$44,U$79,U$78";"WHITE6";6;"";;;
9;"U$26";"GND0";1;"";;;
10;"R3,R2,R7,R5";"0603";4;"330";;;
11;"LOGO16";"SFE_LOGO_NAME_.1";1;"SFE_LOGO_NAME.1_INCH";;;
12;"U$5";"POWER_STRIP0";1;"";;;
13;"U$43";"POWER2";1;"";;;
14;"LOGO8";"REVISION";1;"REVISION";;;
15;"U$37,U$36,U$75";"BLUE4";3;"";;;
16;"D2";"LED-1206";1;"RED";;;
17;"U$50,U$31,U$68,U$70,U$29,U$72,U$69,U$73,U$71";"GATOR#PNG";9;"";;;
18;"LOGO15,LOGO3,LOGO4,LOGO2,LOGO7,LOGO5,LOGO6,LOGO18";"OSHW-LOGO-MINI";8;"OSHW-LOGOMINI";;;
19;"U$35";"STRIP2";1;"";;;
20;"U$9";"GROUND3";1;"";;;
21;"LOGO17,LOGO1,LOGO11,LOGO13,LOGO12,LOGO9,LOGO10,LOGO19";"SFE_LOGO_FLAME_.1";8;"SFE_LOGO_FLAME.1_INCH";;;
22;"U$42,U$41,U$17";"RED2";3;"";;;
23;"D5";"LED-1206";1;"Yellow";;;
24;"U$4";"ORDERING_INSTRUCTIONS";1;"";;;
25;"R6,R4";"0603";2;"150";;;
26;"D6";"LED-1206";1;"GREEN";;;
27;"FD3,FD1,FD2,FD4";"FIDUCIAL-MICRO";4;"FIDUCIALUFIDUCIAL";;;
28;"FRAME1";"CREATIVE_COMMONS";1;"FRAME-LETTER";;;
29;"U$39,U$40,U$67";"GREEN3";3;"";;;
30;"D3,D9";"LED-1206";2;"WHITE";;;
31;"D4";"LED-1206";1;"BLUE";;;
32;"U$51";"GATOR#COLOR0";1;"";;;

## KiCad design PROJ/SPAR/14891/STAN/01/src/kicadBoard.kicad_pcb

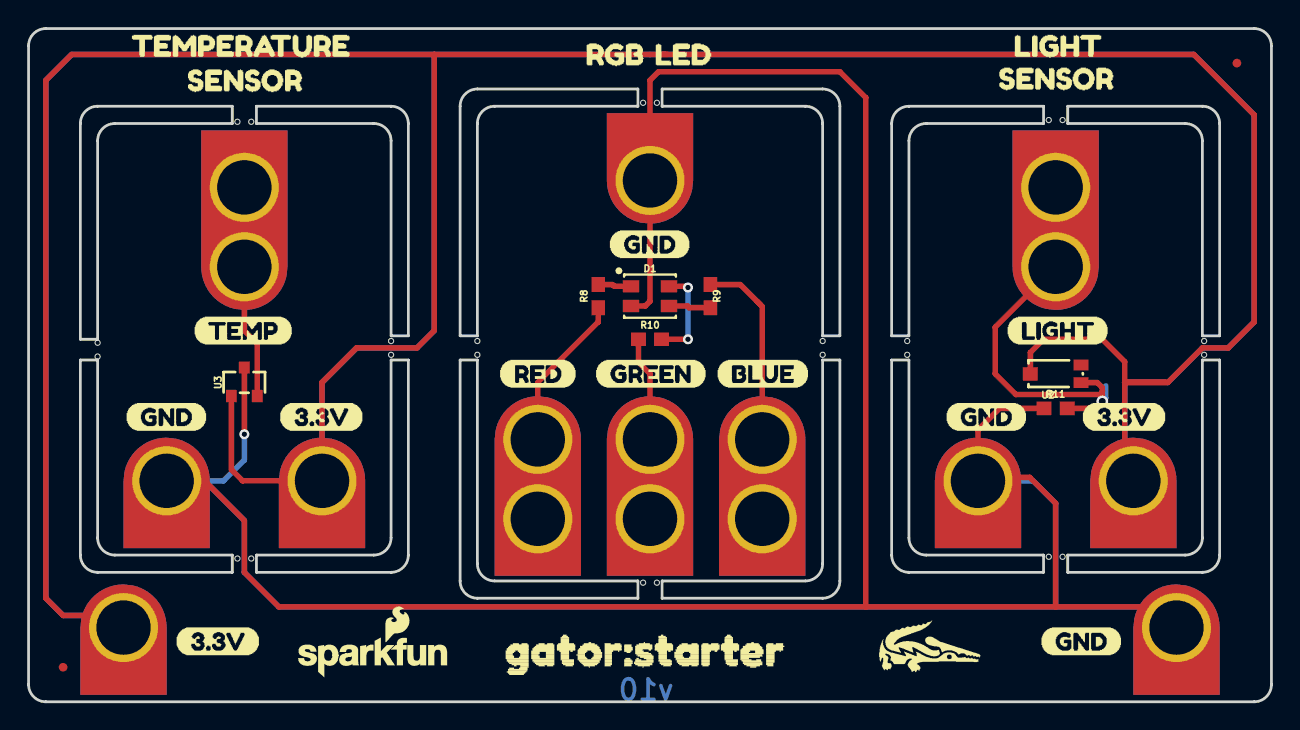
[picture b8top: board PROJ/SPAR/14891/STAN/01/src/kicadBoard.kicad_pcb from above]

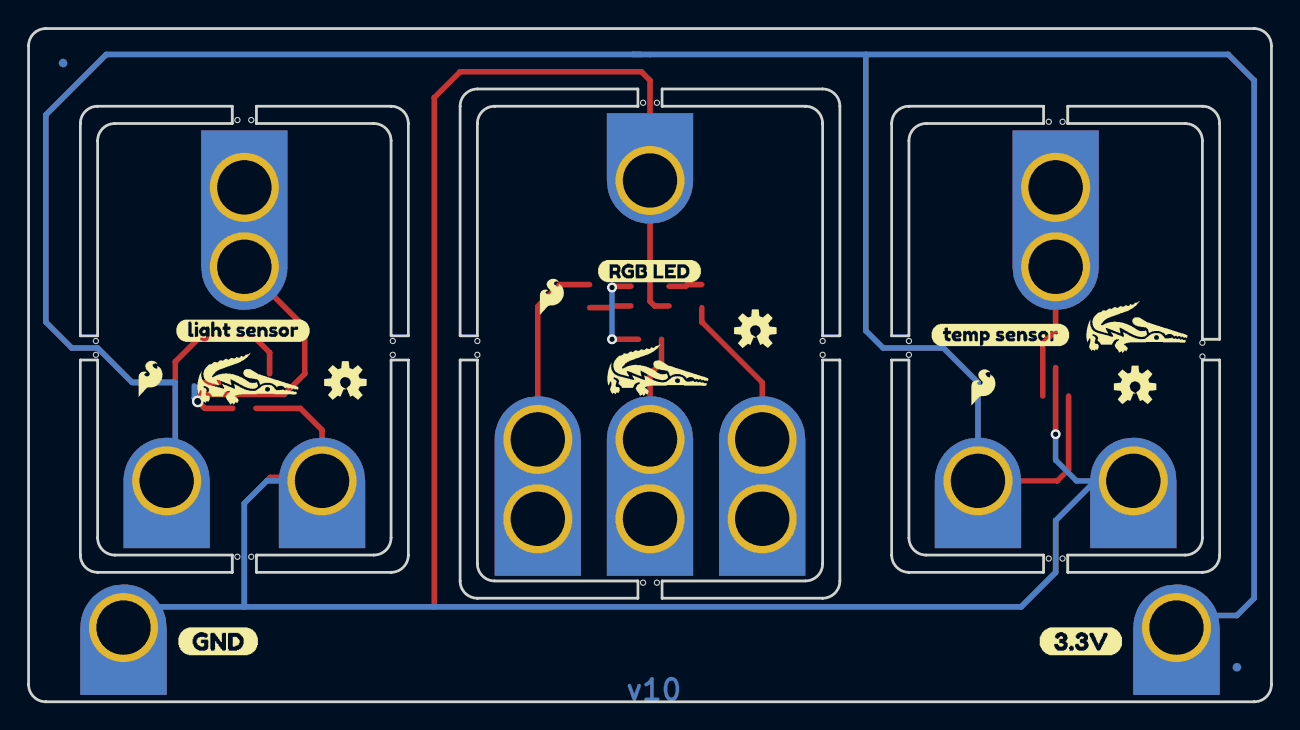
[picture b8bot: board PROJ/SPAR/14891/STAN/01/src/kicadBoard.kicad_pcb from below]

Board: 2 copper layers, 91.4 x 49.5 mm, 85 parts (16 on the bottom side), 10 nets.

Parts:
@HOLE0, @HOLE1, @HOLE2, @HOLE3, @HOLE4, @HOLE5, @HOLE6, @HOLE7, @HOLE8, @HOLE9, @HOLE10, @HOLE11, @HOLE12, @HOLE13, @HOLE14, @HOLE15, @HOLE16, @HOLE17, @HOLE18, @HOLE19, @HOLE20, @HOLE21, @HOLE22, @HOLE23: (no value)
D1: XZM2CRKM2DGFBB45SCCB; PLCC4SMDLED
FD1, FD2, FD3, FD4: FIDUCIALUFIDUCIAL; FIDUCIAL-MICRO
FRAME1: FRAME-LETTER; CREATIVE_COMMONS
LOGO1, LOGO4, LOGO6: SFE_LOGO_FLAME.1_INCH; SFE_LOGO_FLAME_.1
LOGO2, LOGO3, LOGO5: OSHW-LOGOS; OSHW-LOGO-S
LOGO7: REVISION
R8: 200; 0603
R9, R10: 100; 0603
R11: 10k; 0603
U2: LIGHT_SENSORTEMT6000; TEMT6000
U3: MCP9700TT; SOT23-3
U$1, U$6, U$7, U$38, U$39: GND0
U$2, U$3, U$36, U$37: 3#3V1
U$4: BLUE10
U$5: SFE_LOGO_NAME_FLAME_.1
U$8: GREEN9
U$9, U$20: LIGHT4
U$10, U$14, U$15, U$23, U$24: GATOR
U$11, U$12, U$19, U$22, U$25, U$26, U$35: TAB_GATOR_MINI
U$13: TEMP3
U$16, U$21: SENSOR2
U$17: TEMPERATURE3
U$18: RED8
U$27: LED5
U$28, U$29, U$41, U$70: GATOR#PNG
U$30: GATOR#STARTER0
U$31: LIGHT_SENSOR0
U$32: TEMP_SENSOR3
U$33: ORDERING_INSTRUCTIONS
U$34: RGB_LED0
U$40: RGB0

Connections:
3.3V: U2.COLLECTOR, U3.1, U$11.P1, U$19.P1, U$26.P1
GND: D1.4, R11.1, U3.3, U$12.P1, U$22.P1, U$25.P1, U$35.P1
unnamed: U3.2, U$23.P$1, U$23.P$2
unnamed: D1.3, R9.2
unnamed: D1.1, R8.2
unnamed: D1.2, R10.2
unnamed: R8.1, U$10.P$1, U$10.P$2
unnamed: R9.1, U$14.P$1, U$14.P$2
unnamed: R10.1, U$15.P$1, U$15.P$2
unnamed: R11.2, U2.EMITTER, U$24.P$1, U$24.P$2

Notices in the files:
parts and their libraries:
RELEASED UNDER THE CREATIVE COMMONS ATTRIBUTION SHARE-ALIKE 4.0 LICENSE
HTTPS://CREATIVECOMMONS.ORG/LICENSES/BY-SA/4.0
